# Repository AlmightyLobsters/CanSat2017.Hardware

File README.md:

# CanSat Hardware
> Hardware repository for the CanSat 2017 competition

---

_by the **Almighty Lobsters**_

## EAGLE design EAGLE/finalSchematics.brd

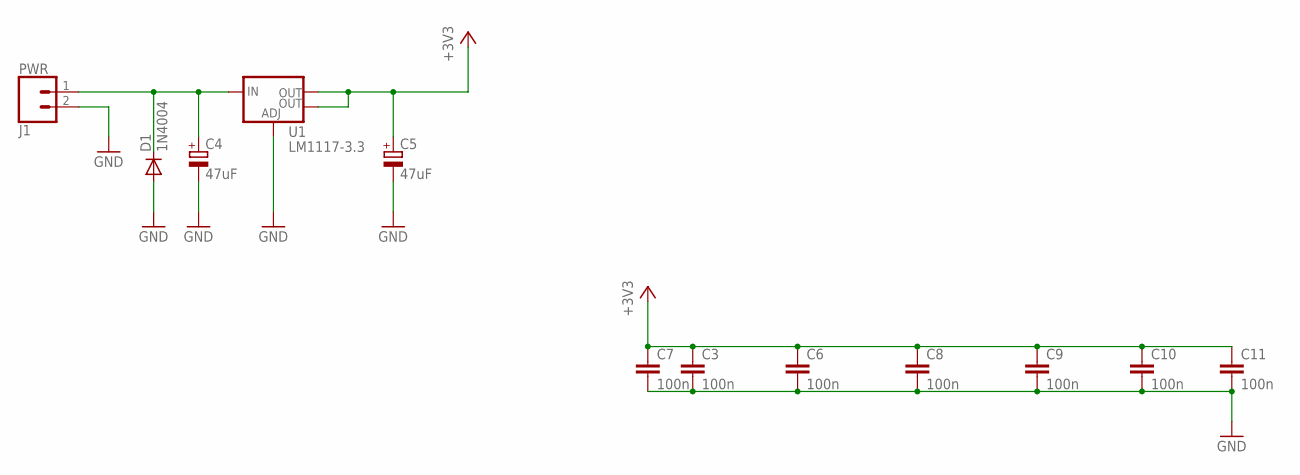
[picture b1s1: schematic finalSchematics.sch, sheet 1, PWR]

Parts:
C3, C6, C7, C8, C9, C10, C11: 100n; C0805
C4, C5: 47uF; 153CLV-0810
D1: 1N4004; DO41-10
J1: PWR; 1X02
U1: LM1117-3.3; SOT223

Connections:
+3V3: C3.1, C5.+, C6.1, C7.1, C8.1, C9.1, C10.1, C11.1, U1.2 (OUT), U1.4 (OUT); also elsewhere on the board
GND: C3.2, C4.-, C5.-, C6.2, C7.2, C8.2, C9.2, C10.2, C11.2, D1.A, J1.2, U1.1 (ADJ); also elsewhere on the board
unnamed: C4.+, D1.C, J1.1, U1.3 (IN)

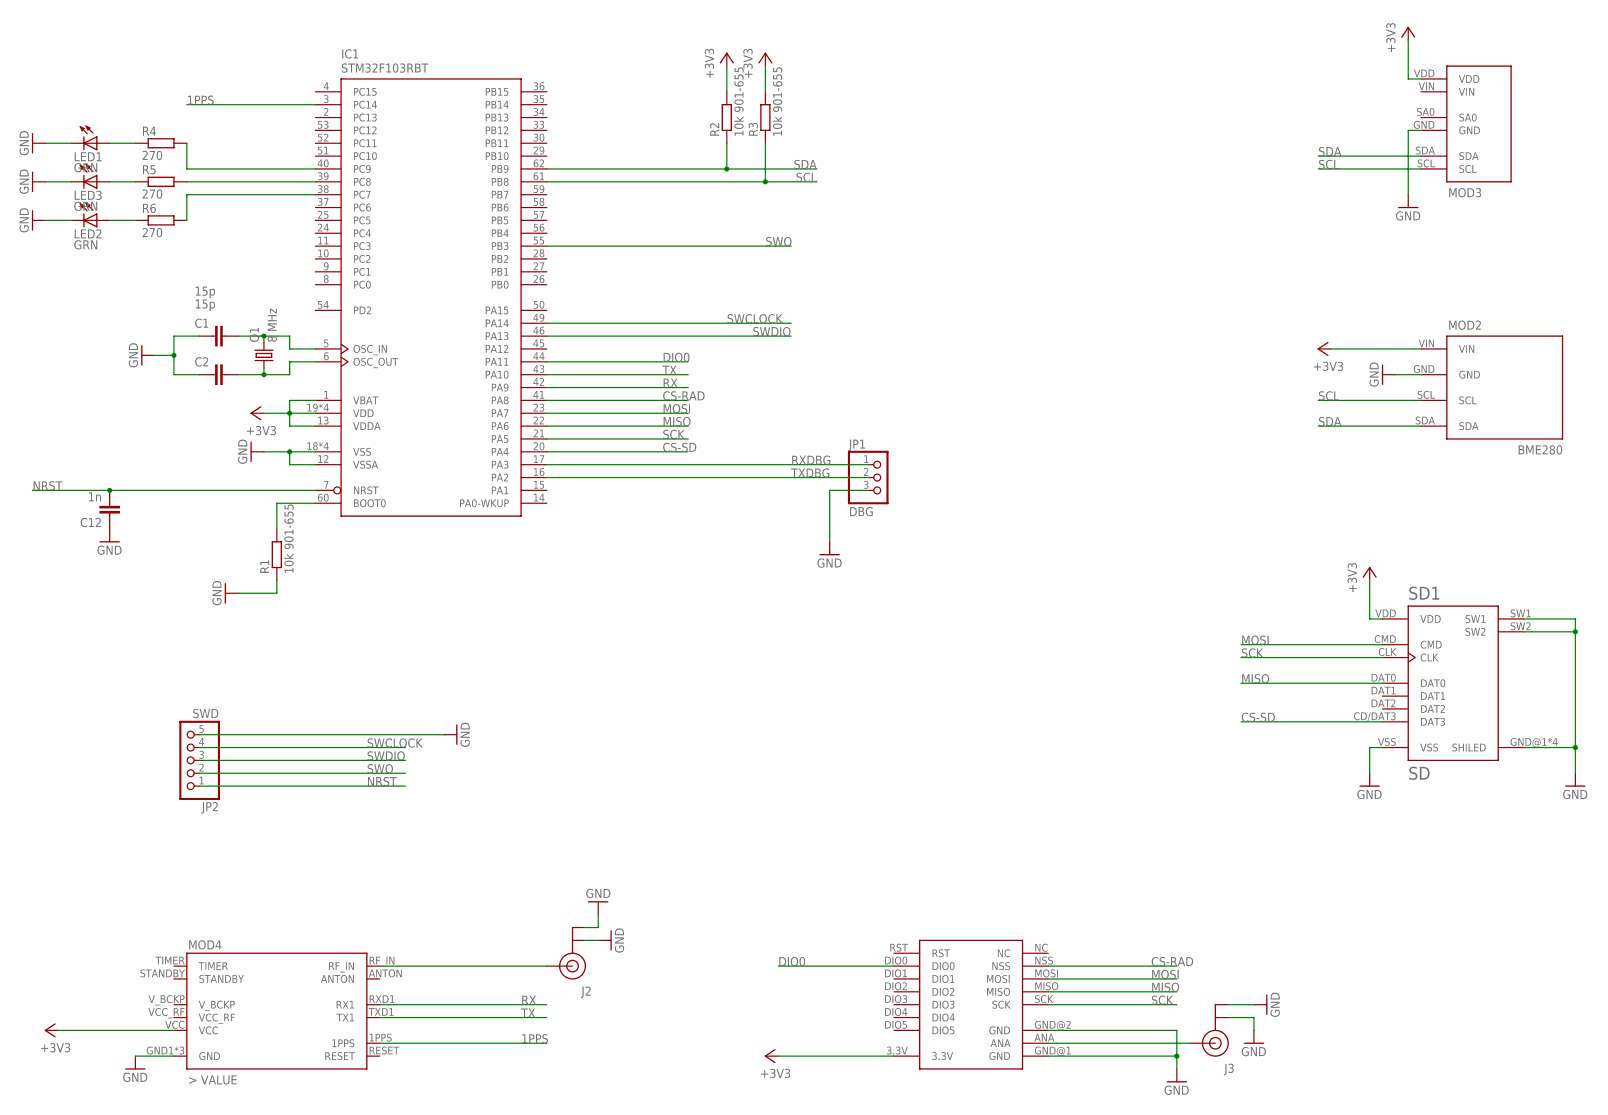
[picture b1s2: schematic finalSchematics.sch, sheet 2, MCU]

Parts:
C1, C2: 15p; C0805
C12: 1n; C0805
IC1: STM32F103RBT; LQFP64
J2, J3: U.FL
JP1: DBG; 1X03
JP2: SWD; 1X05
LED1, LED2, LED3: GRN; CHIP-LED0603
MOD2: BME280
MOD3: IMU04A
MOD4: GPS; L70B-GPS
Q1: 8 MHz; HC49UP
R1, R2, R3: 10k 901-655; R0805
R4, R5, R6: 270; R0805
SD1: SD; MOLEX-SD-104031
U$2: RFM69; 20X16BOARD

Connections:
1PPS: IC1.3 (PC14), MOD4.1PPS
+3V3: IC1.1 (VBAT), IC1.13 (VDDA), IC1.19 (VDD), IC1.32 (VDD), IC1.48 (VDD), IC1.64 (VDD), MOD2.VIN, MOD3.VDD, MOD4.VCC, R2.2, R3.2, SD1.VDD, U$2.3.3V; also elsewhere on the board
CS-RAD: IC1.41 (PA8), U$2.NSS
CS-SD: IC1.20 (PA4), SD1.CD/DAT3 (DAT3)
DIO0: IC1.44 (PA11), U$2.DIO0
GND: C1.1, C2.1, C12.1, IC1.12 (VSSA), IC1.18 (VSS), IC1.31 (VSS), IC1.47 (VSS), IC1.63 (VSS), J2.P$1 (GND), J2.P$2 (GND), J3.P$1 (GND), J3.P$2 (GND), JP1.3, JP2.5, LED1.C, LED2.C, LED3.C, MOD2.GND, MOD3.GND, MOD4.GND1 (GND), MOD4.GND2 (GND), MOD4.GND3 (GND), R1.1, SD1.GND@1 (SHILED), SD1.GND@2 (SHILED), SD1.GND@3 (SHILED), SD1.GND@4 (SHILED), SD1.SW1, SD1.SW2, SD1.VSS, U$2.GND@1 (GND), U$2.GND@2 (GND); also elsewhere on the board
MISO: IC1.22 (PA6), SD1.DAT0, U$2.MISO
MOSI: IC1.23 (PA7), SD1.CMD, U$2.MOSI
unnamed: C2.2, IC1.6 (OSC_OUT), Q1.1
unnamed: C1.2, IC1.5 (OSC_IN), Q1.2
unnamed: J3.P$3 (SIGNAL), U$2.ANA
unnamed: J2.P$3 (SIGNAL), MOD4.RF_IN
unnamed: IC1.38 (PC7), R6.2
unnamed: IC1.39 (PC8), R5.2
unnamed: IC1.40 (PC9), R4.2
unnamed: LED1.A, R4.1
unnamed: LED2.A, R6.1
unnamed: LED3.A, R5.1
unnamed: IC1.60 (BOOT0), R1.2
NC: U$2.NC
NRST: C12.2, IC1.7 (NRST), JP2.1
RX: IC1.42 (PA9), MOD4.RXD1 (RX1)
RXDBG: IC1.17 (PA3), JP1.1
SCK: IC1.21 (PA5), SD1.CLK, U$2.SCK
SCL: IC1.61 (PB8), MOD2.SCL, MOD3.SCL, R3.1
SDA: IC1.62 (PB9), MOD2.SDA, MOD3.SDA, R2.1
SWCLOCK: IC1.49 (PA14), JP2.4
SWDIO: IC1.46 (PA13), JP2.3
SWO: IC1.55 (PB3), JP2.2
TX: IC1.43 (PA10), MOD4.TXD1 (TX1)
TXDBG: IC1.16 (PA2), JP1.2

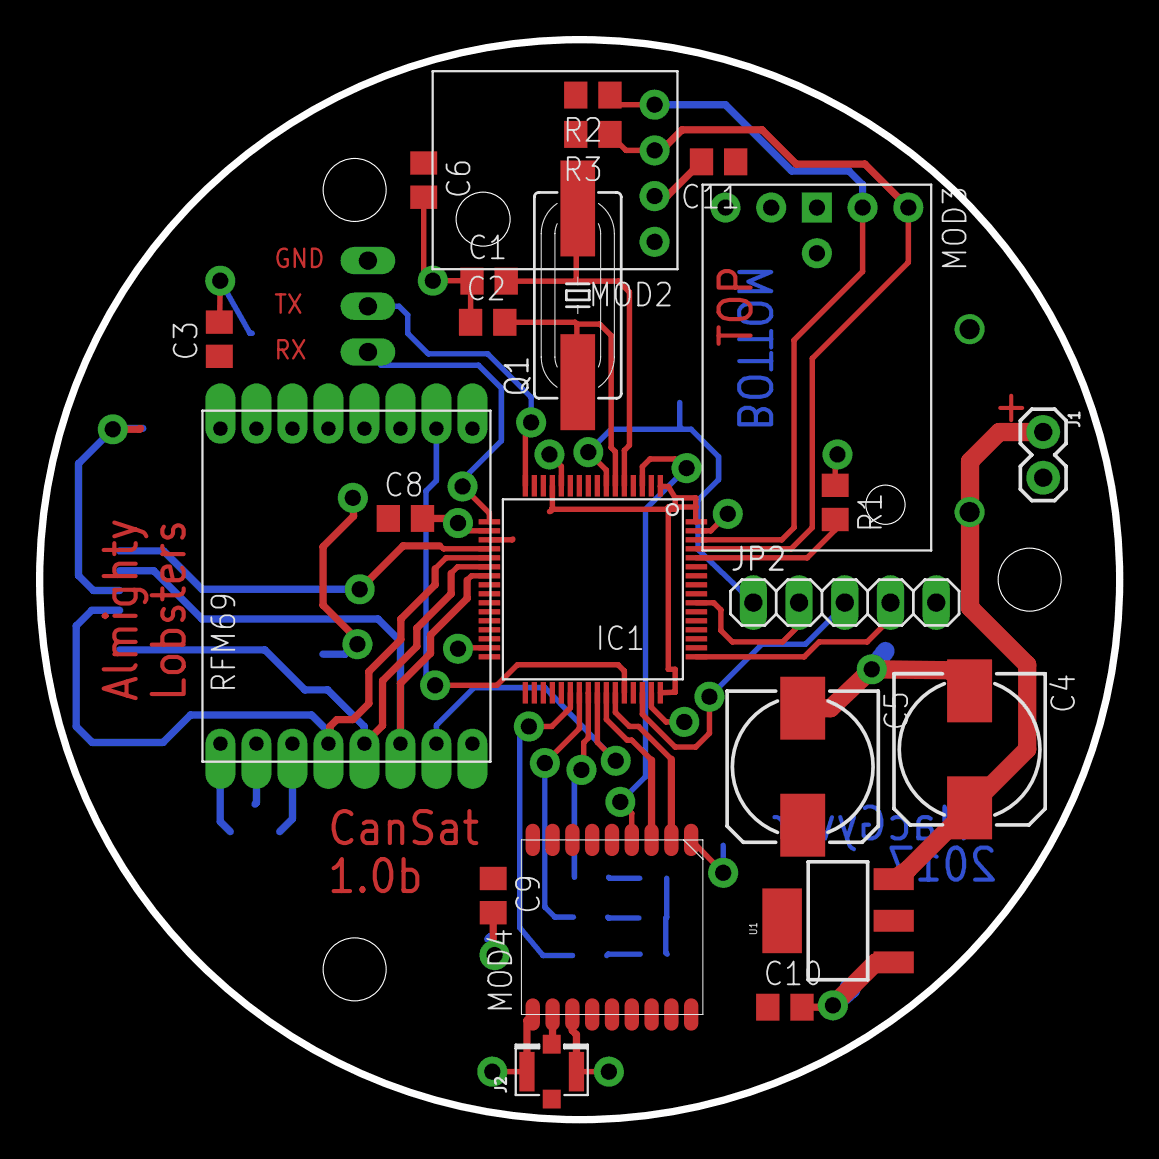
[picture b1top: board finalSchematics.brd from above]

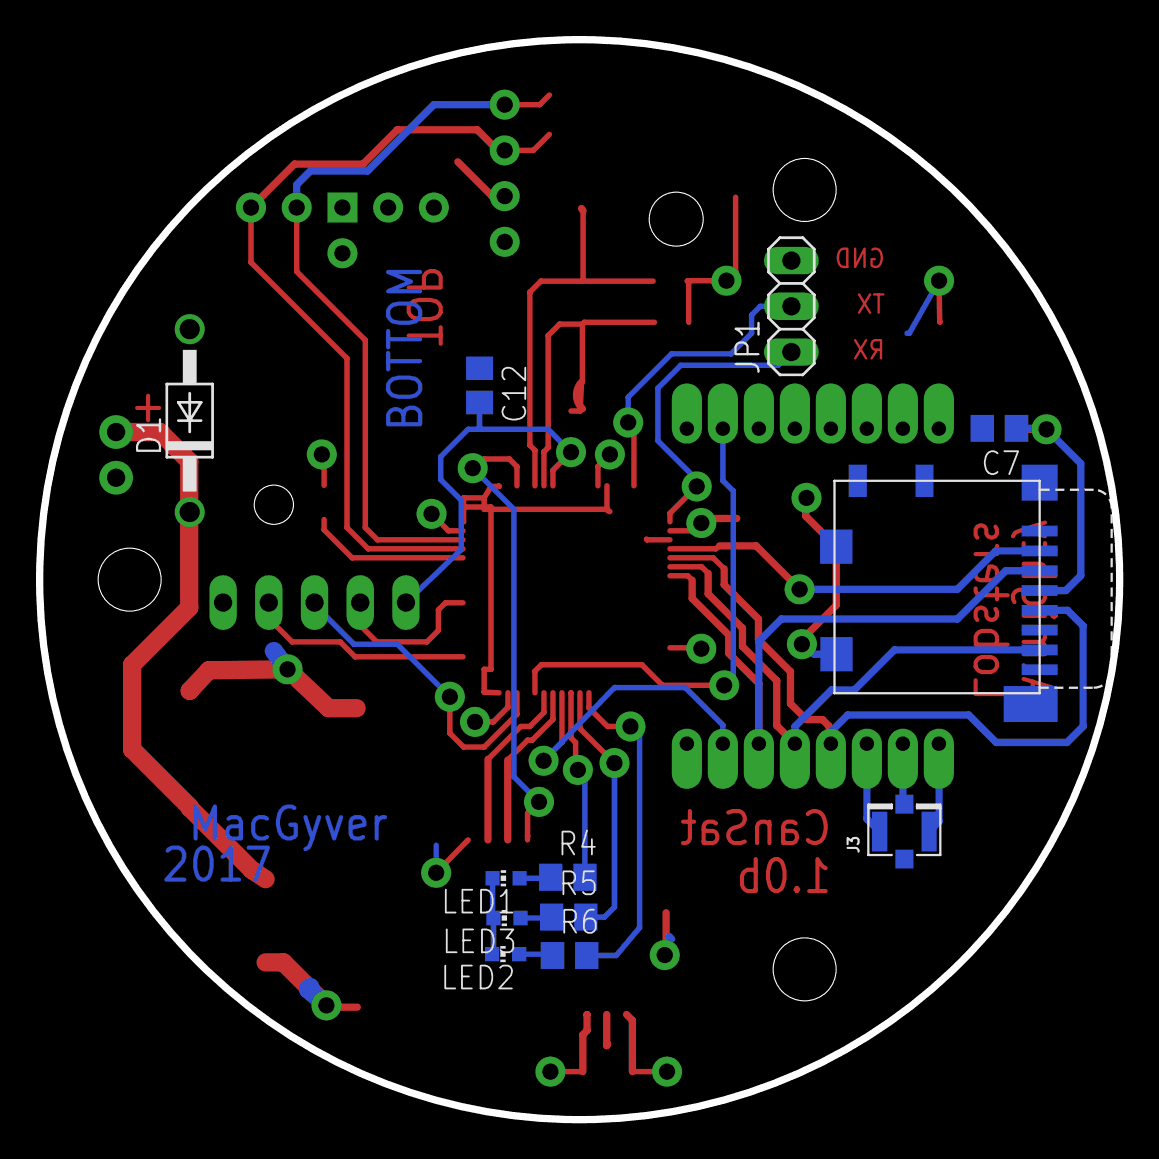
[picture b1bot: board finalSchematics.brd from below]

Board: 2 copper layers, 60.0 x 60.0 mm, 35 parts (12 on the bottom side), 31 nets.

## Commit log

2017-02-07 Created readme and added ZenHub badge
2017-03-13 Eagle file ready for meeting with Vojta S.
    Missing GPS module footer. Our module is L70 and only L80 library was
    found. Will have to resolve later by creating a library at Mucirna.
    Repositories folder updated with new documentation
2017-03-14 SDfixed, Gyro fixed
2017-03-14 Update documentation structure
2017-03-18 Update
    WIP
2017-03-18 Add GPS components
2017-03-18 Update BME280 library
    Created BME280 part for EAGLE PCB
2017-03-18 Datasheet for MinIMU-9 v5 Gyro
2017-03-18 Move library a level lower
    Silly humans
2017-03-18 Add Sparkfun eagle libs
2017-03-18 Finish modules
    All modules except SD card imported in the schematic. Board still to-do
2017-03-19 Add SD package, fix powers supply of MCU
2017-03-21 Connect modules
2017-03-22 Final schematic ready to control
    Start creating the board itself
2017-03-23 Death is near
    Routing the board
2017-03-23 Finish Route PCB, prepare for inspection
    Hakys je sport budoucnosti!
2017-03-23 Fix route overlap
2017-03-24 Small fix (overlap, clearance)
2017-03-25 Final fixes before etching

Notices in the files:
parts and their libraries:
SparkFun-Connectors: Licensing: Creative Commons ShareAlike 4.0 International - https://creativecommons.org/licenses/by-sa/4.0
